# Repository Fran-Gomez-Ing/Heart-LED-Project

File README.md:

# Heart-LED-Project
Heart-shaped LED badge with integrated Li-ion battery charging system.

A self-initiated project to bridge the gap between theory and hardware. I designed, routed, and hand-assembled this PCB from scratch. It’s a portable, rechargeable system featuring:

Power: Portable system featuring a Li-ion battery with an integrated charging circuit (TP4056).

Architecture: Discrete LED array driven by an NE555 timer on a custom-shaped, double-layer PCB.

Toolchain: KiCad 9.0.

What I Learned:

End-to-End Workflow: Moved from theory to a physical product by managing the full cycle: footprints, BOM, and Gerber generation for manufacturing.

Component Selection: Mastered reading datasheets to select appropriate ICs, like the TP4056 for charging and the NE555 timer for logic.

DFA (Design for Assembly): Implemented HandSolder footprints with enlarged pads to ensure reliable manual assembly and easier debugging.

Power Integration: Gained practical experience with Li-ion battery management and USB power standards.

Possible Improvements:

Battery Safety: V1.0 focuses on the charging cycle. In the next iteration, I will add a DW01A protection IC and 8205A MOSFETs to prevent undervoltage (below 2.4V) and ensure battery longevity.

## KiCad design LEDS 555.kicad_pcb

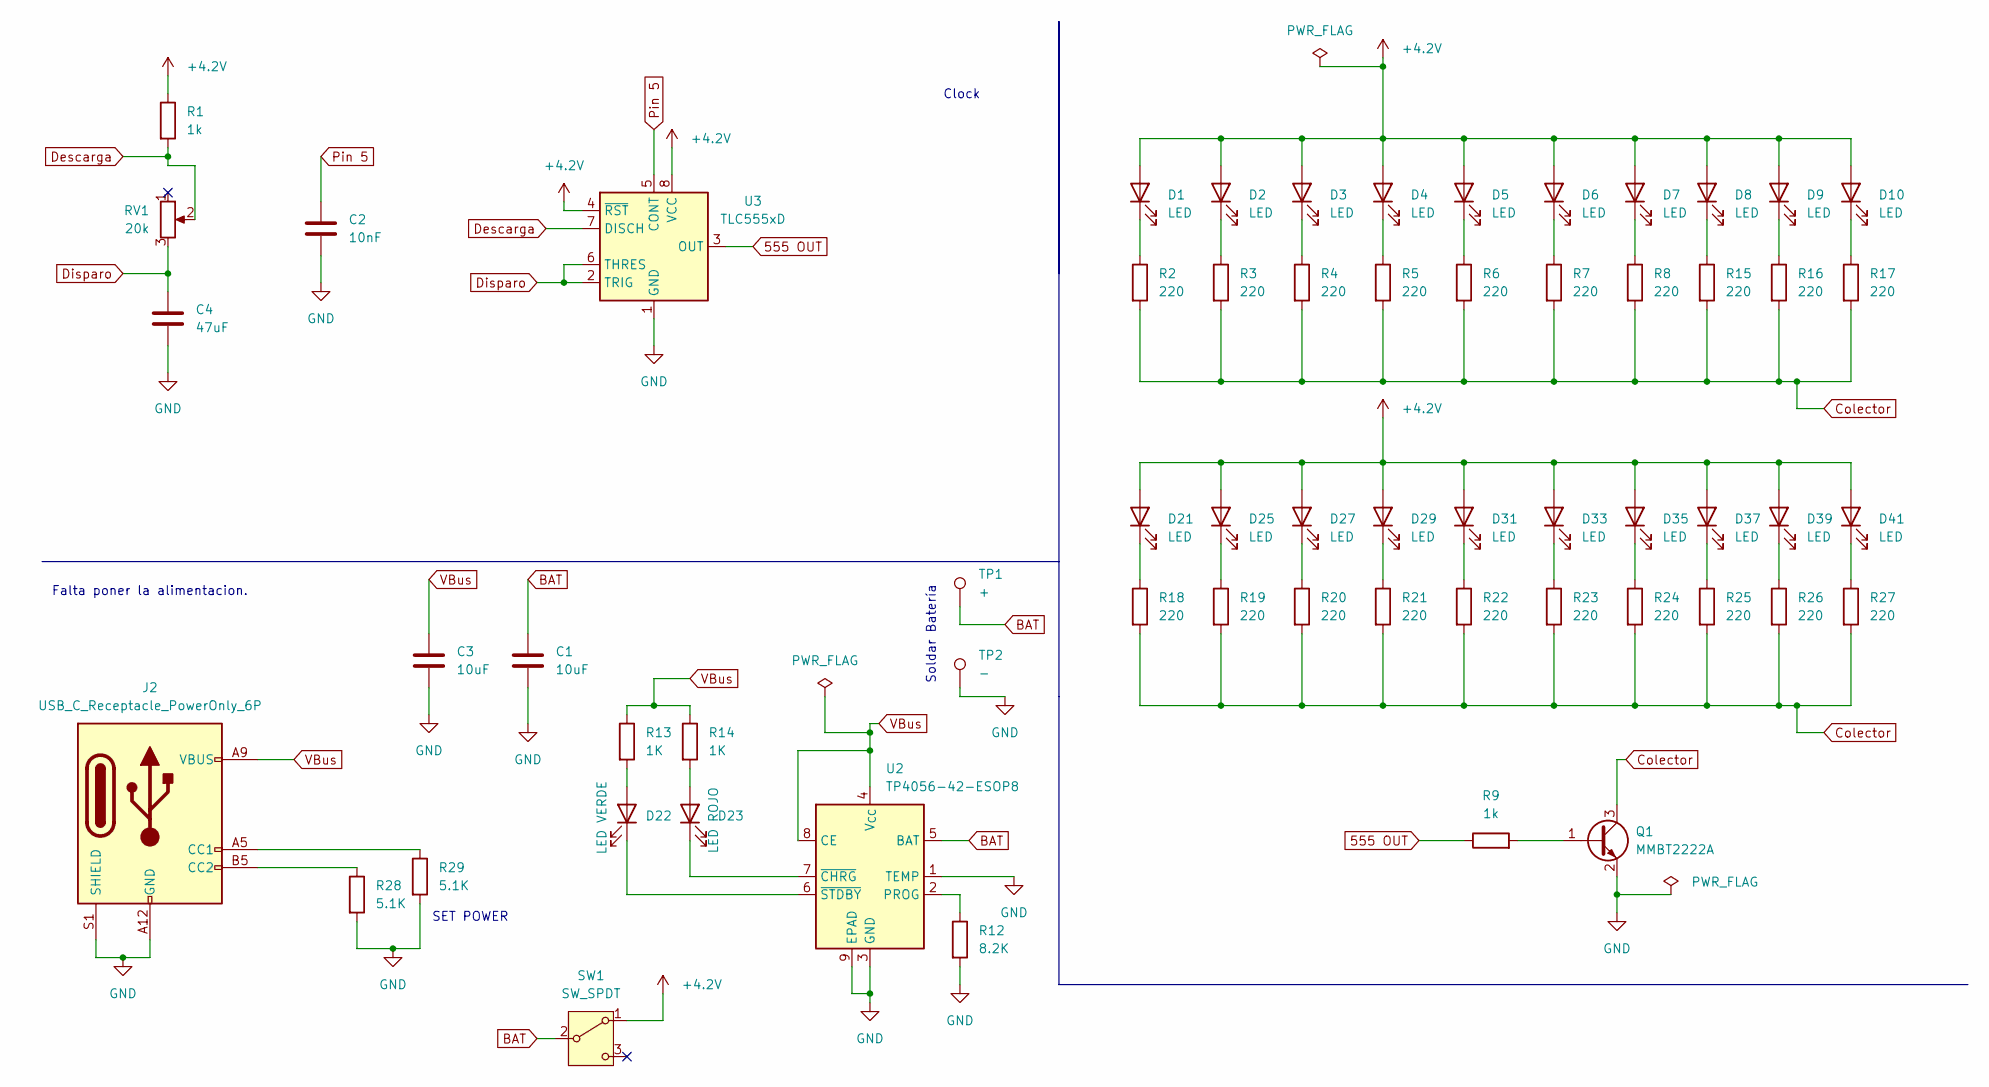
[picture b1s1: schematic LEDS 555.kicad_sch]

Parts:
C1, C3: 10uF; C_0805_2012Metric_Pad1.18x1.45mm_HandSolder; LCSC C440198
C2: 10nF; C_0805_2012Metric_Pad1.18x1.45mm_HandSolder; LCSC C83170
C4: 47uF; C_0805_2012Metric_Pad1.18x1.45mm_HandSolder; LCSC C16780
D1, D2, D3, D4, D5, D6, D7, D8, D9, D10, D21, D25, D27, D29, D31, D33, D35, D37, D39, D41: LED; LED_D3.0mm; LCSC C2895492
D22: LED VERDE; LED_0805_2012Metric_Pad1.15x1.40mm_HandSolder; LCSC C25170728
D23: LED ROJO; LED_0805_2012Metric_Pad1.15x1.40mm_HandSolder; LCSC C19171391
J2: USB_C_Receptacle_PowerOnly_6P; USB_C_Receptacle_GCT_USB4135-GF-A_6P_TopMnt_Horizontal; LCSC C5438410
Q1: MMBT2222A; SOT-23; LCSC C82460
R1, R9: 1k; R_0805_2012Metric_Pad1.20x1.40mm_HandSolder; LCSC C17513
R2, R3, R4, R5, R6, R7, R8, R15, R16, R17, R18, R19, R20, R21, R22, R23, R24, R25, R26, R27: 220; R_0805_2012Metric_Pad1.20x1.40mm_HandSolder; LCSC C17557
R12: 8.2K; R_0805_2012Metric_Pad1.20x1.40mm_HandSolder; LCSC C17828
R13, R14: 1K; R_0805_2012Metric_Pad1.20x1.40mm_HandSolder; LCSC C17513
R28, R29: 5.1K; R_0805_2012Metric_Pad1.20x1.40mm_HandSolder; LCSC C27834
RV1: 20k; Potentiometer_Alps_RK09K_Single_Vertical; LCSC C470290
SW1: SW_SPDT; SW_SPDT_PCM12; LCSC C221841
TP1: +; TestPoint_Pad_D2.0mm
TP2: -; TestPoint_Pad_D2.0mm
U2: TP4056-42-ESOP8; SOIC-8-1EP_3.9x4.9mm_P1.27mm_EP2.41x3.3mm_ThermalVias; LCSC C16581
U3: TLC555xD; SOIC-8_3.9x4.9mm_P1.27mm; LCSC C6986

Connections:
555 OUT: R9.1, U3.3 (OUT)
+4.2V: D1.2 (A), D2.2 (A), D3.2 (A), D4.2 (A), D5.2 (A), D6.2 (A), D7.2 (A), D8.2 (A), D9.2 (A), D10.2 (A), D21.2 (A), D25.2 (A), D27.2 (A), D29.2 (A), D31.2 (A), D33.2 (A), D35.2 (A), D37.2 (A), D39.2 (A), D41.2 (A), R1.1, SW1.1 (A), U3.4 (~RST), U3.8 (VCC)
BAT: C1.1, SW1.2 (B), TP1.1, U2.5 (BAT)
Colector: Q1.3 (C), R2.2, R3.2, R4.2, R5.2, R6.2, R7.2, R8.2, R15.2, R16.2, R17.2, R18.2, R19.2, R20.2, R21.2, R22.2, R23.2, R24.2, R25.2, R26.2, R27.2
Descarga: R1.2, RV1.2, U3.7 (DISCH)
Disparo: C4.1, RV1.3, U3.2 (TRIG), U3.6 (THRES)
GND: C1.2, C2.2, C3.2, C4.2, J2.A12 (GND), J2.B12 (GND), J2.S1 (SHIELD), Q1.2 (E), R12.2, R28.2, R29.2, TP2.1, U2.1 (TEMP), U2.3 (GND), U2.9 (EPAD), U3.1 (GND)
unnamed: D1.1 (K), R2.1
unnamed: D2.1 (K), R3.1
unnamed: D3.1 (K), R4.1
unnamed: D4.1 (K), R5.1
unnamed: D5.1 (K), R6.1
unnamed: D6.1 (K), R7.1
unnamed: D7.1 (K), R8.1
unnamed: D8.1 (K), R15.1
unnamed: D9.1 (K), R16.1
unnamed: D10.1 (K), R17.1
unnamed: D21.1 (K), R18.1
unnamed: D22.2 (A), R13.2
unnamed: D22.1 (K), U2.6 (~STDBY)
unnamed: D23.2 (A), R14.2
unnamed: D23.1 (K), U2.7 (~CHRG)
unnamed: D25.1 (K), R19.1
unnamed: D27.1 (K), R20.1
unnamed: D29.1 (K), R21.1
unnamed: D31.1 (K), R22.1
unnamed: D33.1 (K), R23.1
unnamed: D35.1 (K), R24.1
unnamed: D37.1 (K), R25.1
unnamed: D39.1 (K), R26.1
unnamed: D41.1 (K), R27.1
unnamed: J2.A5 (CC1), R29.1
unnamed: J2.B5 (CC2), R28.1
unnamed: Q1.1 (B), R9.2
unnamed: R12.1, U2.2 (PROG)
Pin 5: C2.1, U3.5 (CONT)
VBus: C3.1, J2.A9 (VBUS), J2.B9 (VBUS), R13.1, R14.1, U2.4 (V_{CC}), U2.8 (CE)

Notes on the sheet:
Clock
Soldar Batería
SET POWER
Falta poner la alimentacion.

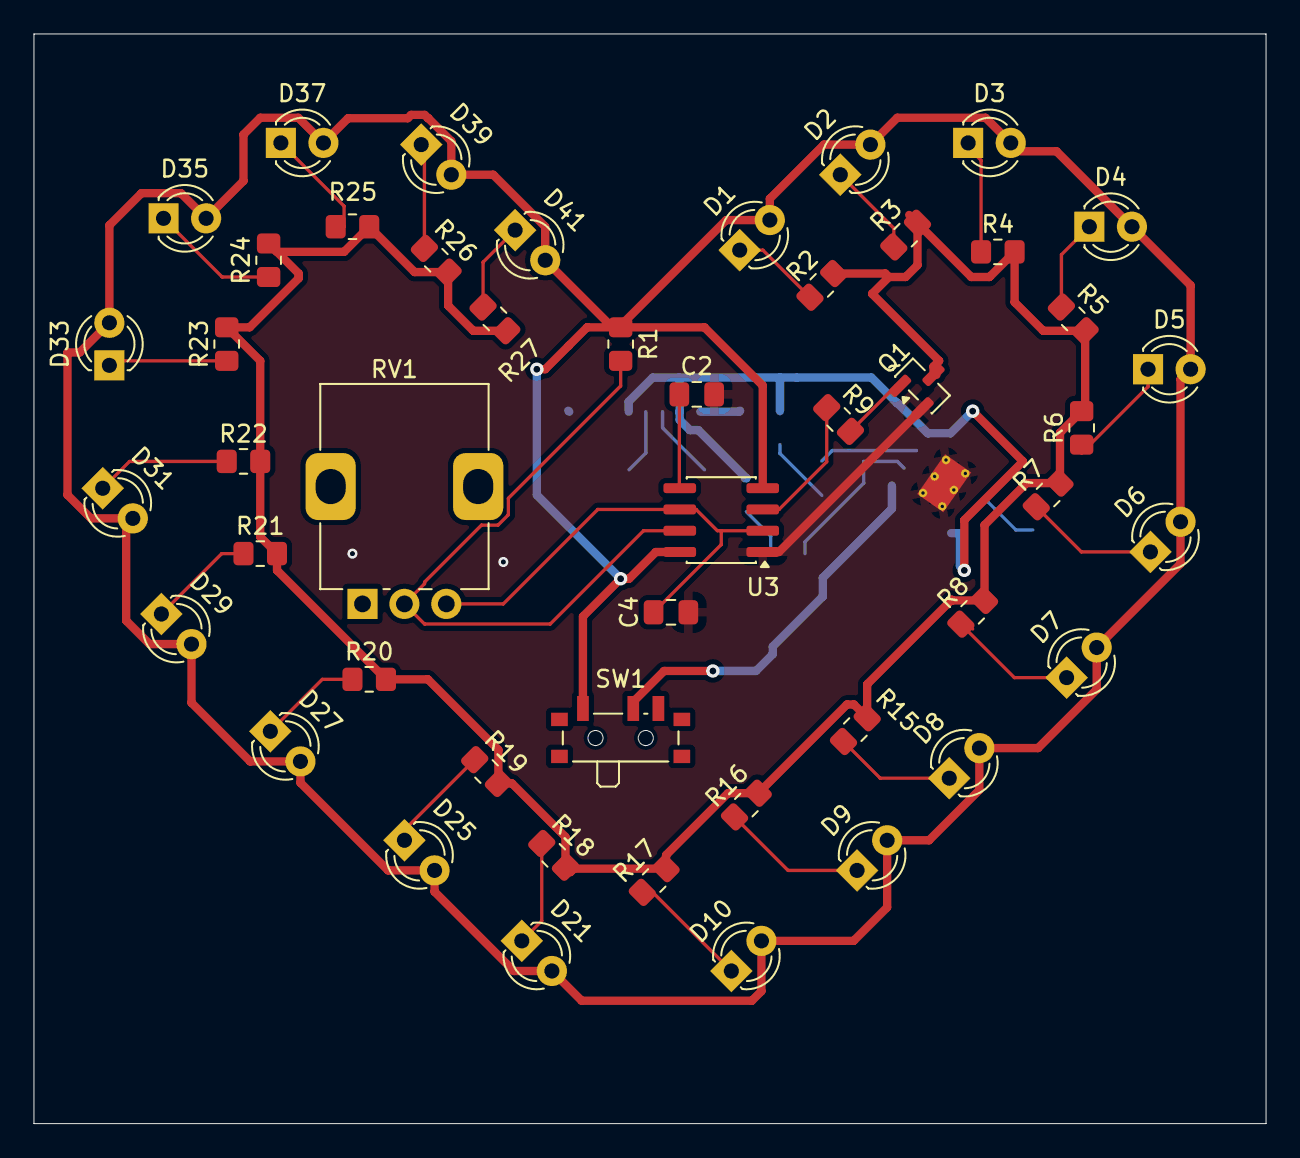
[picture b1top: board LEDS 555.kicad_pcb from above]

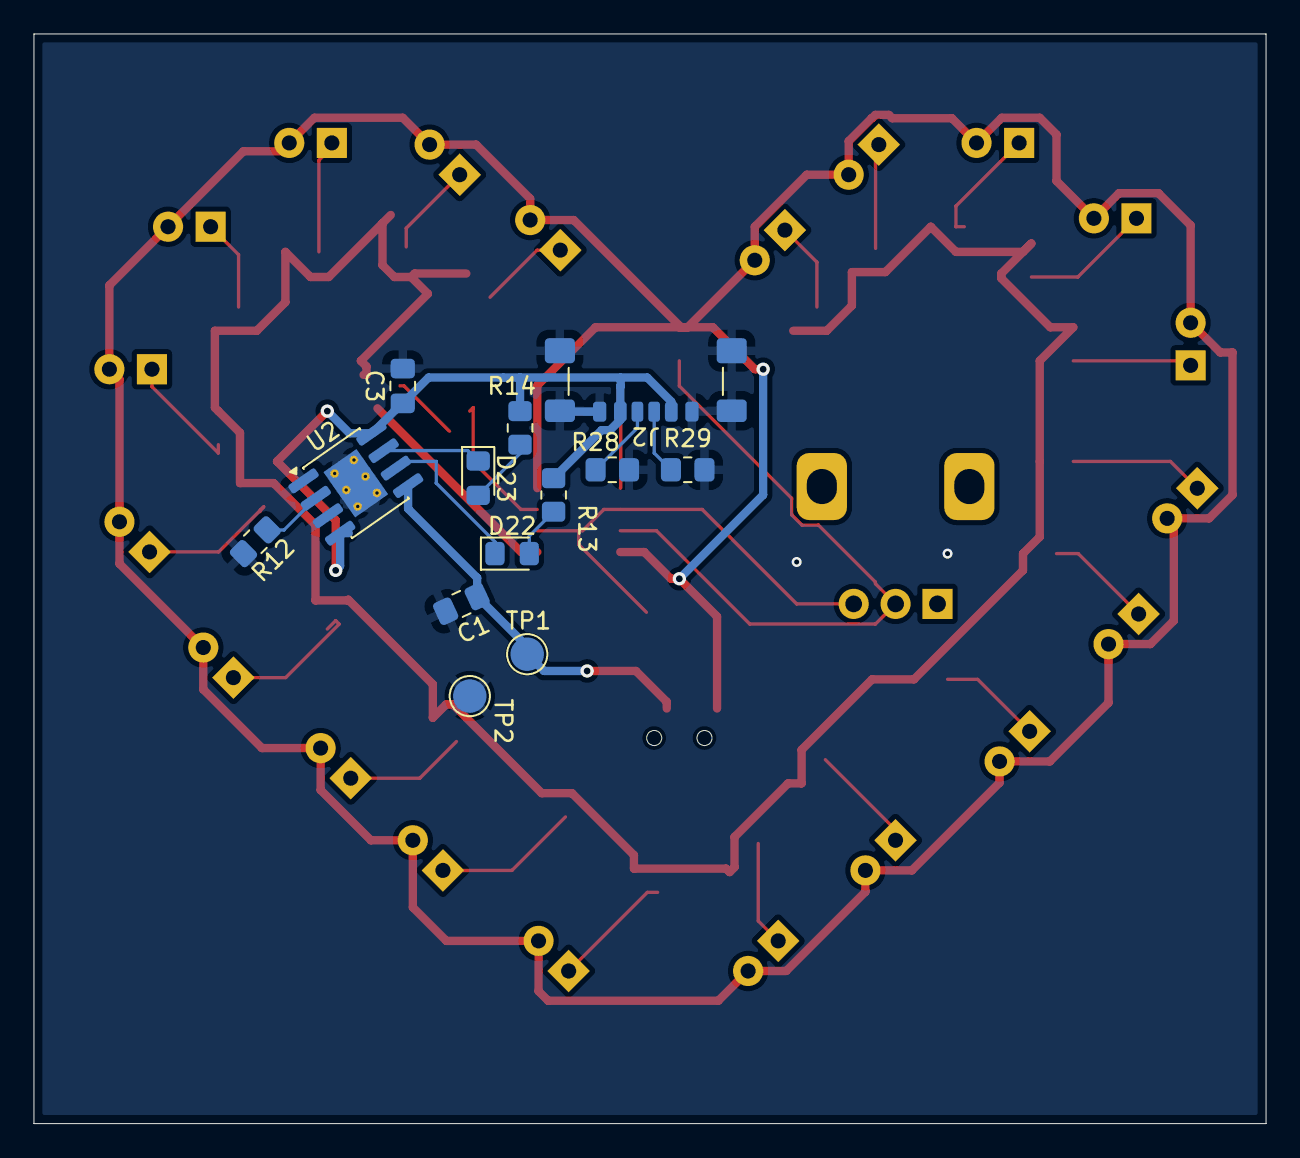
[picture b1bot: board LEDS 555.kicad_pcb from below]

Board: 2 copper layers, 73.5 x 65.0 mm, 61 parts (13 on the bottom side), 37 nets.

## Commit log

2026-03-08 Enhance README with project details and learnings
